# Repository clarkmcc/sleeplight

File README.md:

# SleepLight

SleepLight is a BLE-connected bedside light built around an ESP32-C3, with an iOS companion app for color and brightness control.

## Repository layout

- `firmware/` - Rust firmware for the ESP32-C3 (BLE peripheral + LED ring control).
- `ios/` - SwiftUI iOS app that scans, connects, and sends color/brightness updates over BLE.
- `hardware/` - KiCad project, manufacturing outputs, and mechanical assets (`.kicad_*`, Gerbers, STEP/STL).
- `silkscreen.ai` - Illustrator source for silkscreen/artwork.

## Quick start

### 1) Firmware (ESP32-C3)

Prereqs:
- Rust toolchain (stable) with `riscv32imc-unknown-none-elf`
- `probe-rs` installed
- ESP32-C3 board connected via debug probe

From `firmware/`:

```bash
cargo run
```

This uses the configured runner (`probe-rs run --chip esp32c3 ...`) to build and flash.

### 2) iOS app

Prereqs:
- Xcode (current version)
- iOS device or simulator with Bluetooth support (device recommended)

Open and run:
- `ios/SleepLight.xcodeproj`
- Select the `SleepLight` target and run.

The app scans for a BLE peripheral named `SleepLight` and controls RGB + brightness.

## Current BLE contract

- Peripheral name: `SleepLight`
- Light service UUID: `f3e0c001-8b6f-4d2e-a2d0-6b9c3f2a0000`
- State characteristic UUID: `f3e0c002-8b6f-4d2e-a2d0-6b9c3f2a0000`
- Payload format: 4 bytes `[R, G, B, brightness]`

## Licensing

See [licenses](./LICENSES/README.md) for scope mapping.

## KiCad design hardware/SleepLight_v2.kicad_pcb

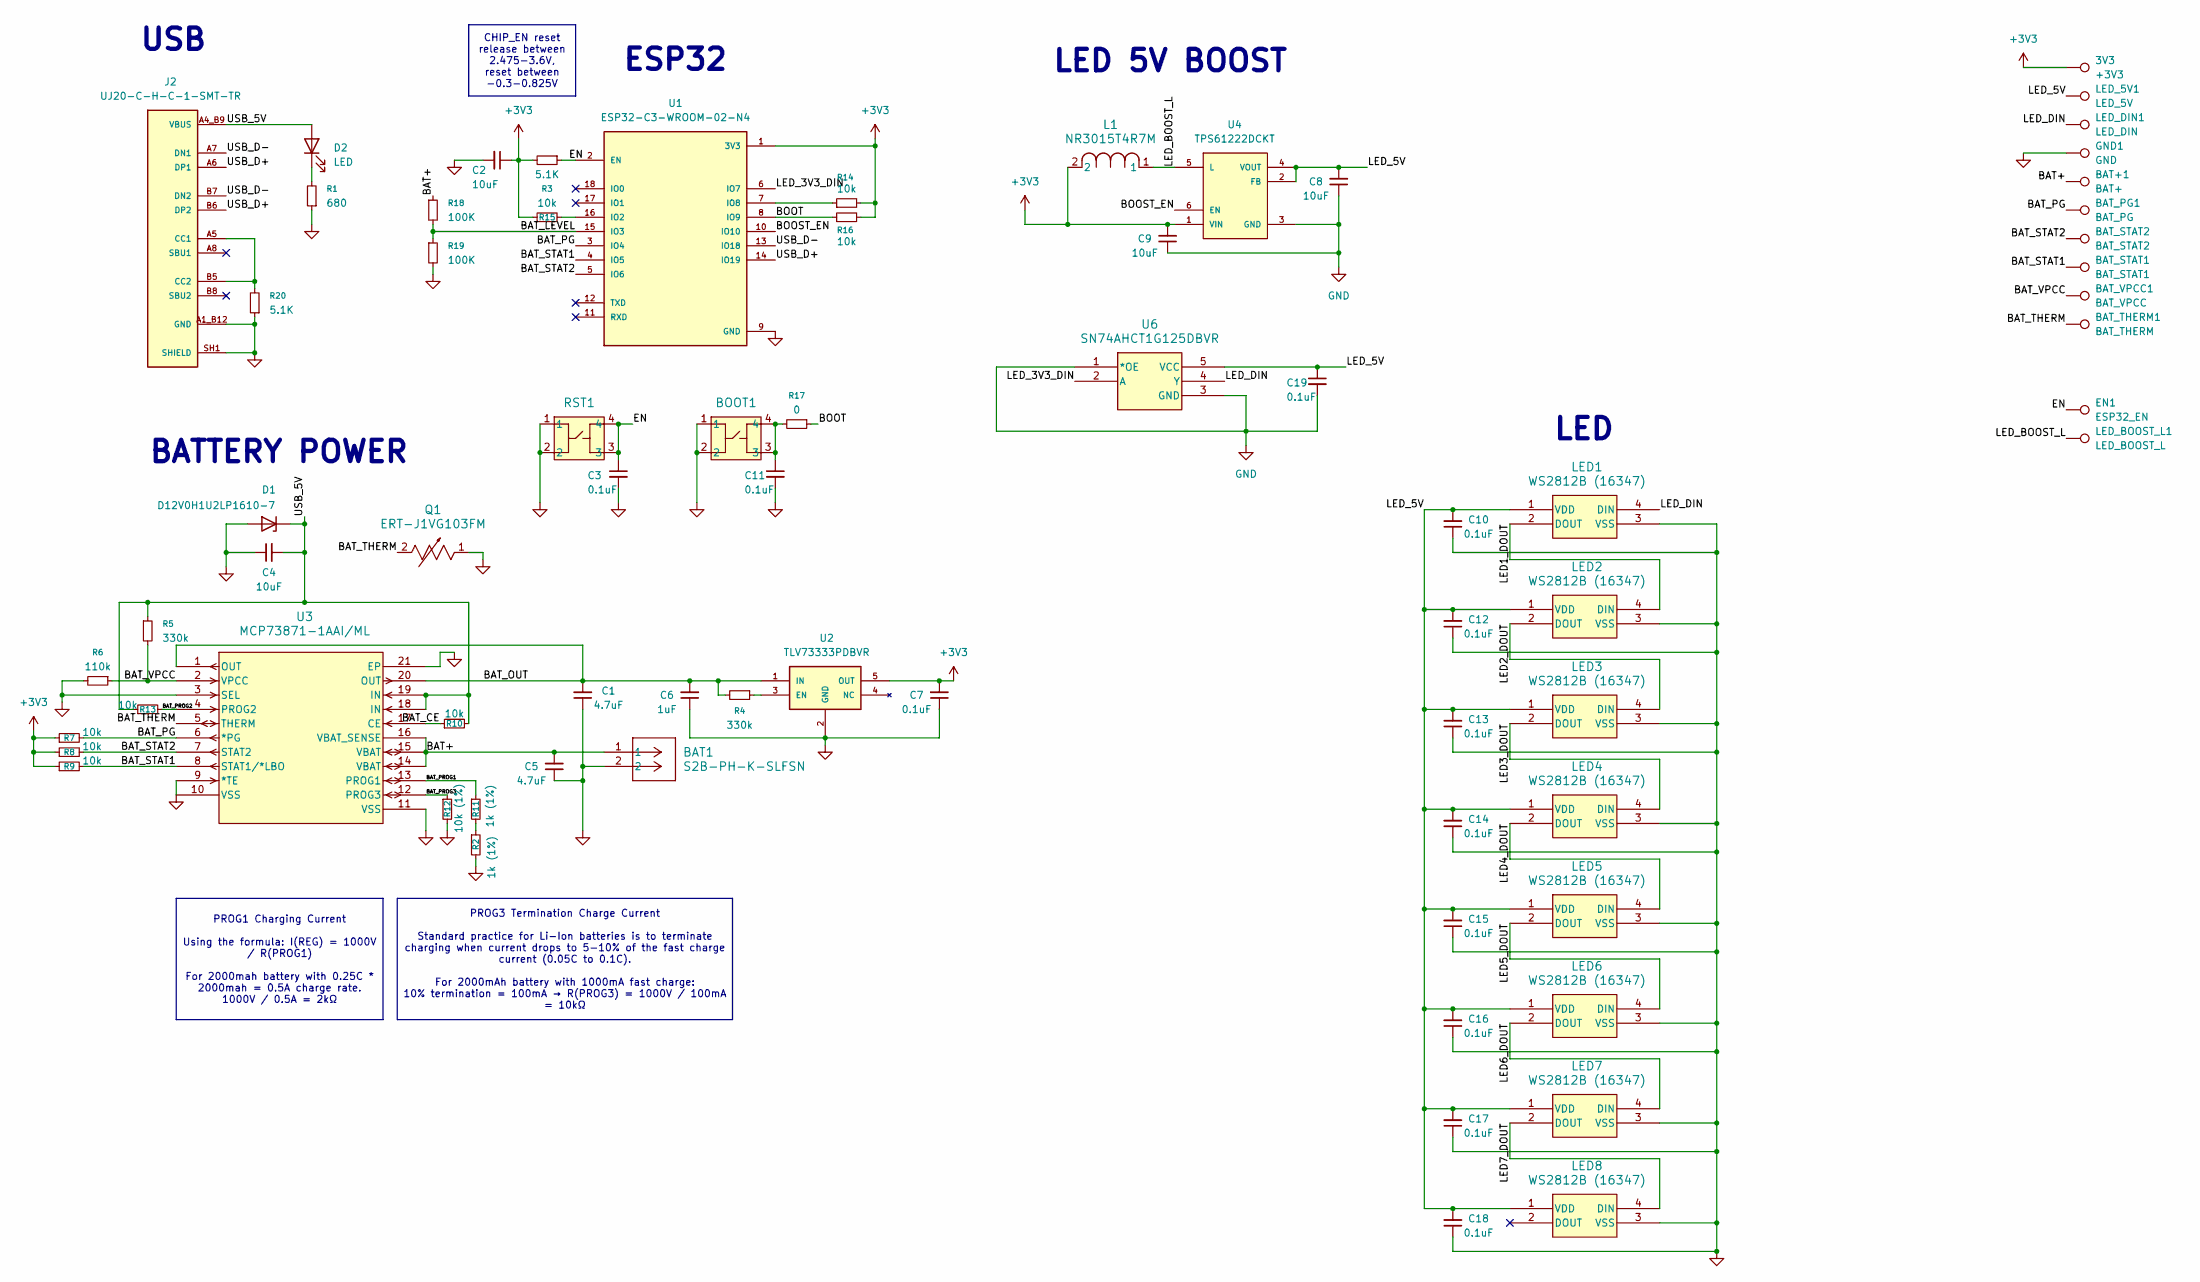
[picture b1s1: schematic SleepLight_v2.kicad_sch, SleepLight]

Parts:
3V3: +3V3; TestPoint_Pad_1.5x1.5mm
BAT1: S2B-PH-K-SLFSN; CONN_S2B-PH-K-S_JST
BAT+1: BAT+; TestPoint_Pad_1.5x1.5mm
BAT_PG1: BAT_PG; TestPoint_Pad_1.5x1.5mm
BAT_STAT1: BAT_STAT1; TestPoint_Pad_1.5x1.5mm
BAT_STAT2: BAT_STAT2; TestPoint_Pad_1.5x1.5mm
BAT_THERM1: BAT_THERM; TestPoint_Pad_1.5x1.5mm
BAT_VPCC1: BAT_VPCC; TestPoint_Pad_1.5x1.5mm
BOOT1: PTS526 SM15 SMTR2 LFS; SON4_PTS526 SM15 SMTR2 LFS_CNK
C1, C5: 4.7uF; C_0603_1608Metric
C2, C4, C8, C9: 10uF; C_0603_1608Metric
C3, C7, C10, C11, C12, C13, C14, C15, C16, C17, C18, C19: 0.1uF; C_0603_1608Metric
C6: 1uF; C_0603_1608Metric
D1: D12V0H1U2LP1610-7; D_0603_1608Metric; DigiKey_Part_Number D12V0H1U2LP1610-7DICT-ND
D2: LED; LED_0603_1608Metric; DigiKey_Part_Number 160-1478-1-ND
EN1: ESP32_EN; TestPoint_Pad_1.5x1.5mm
GND1: GND; TestPoint_Pad_1.5x1.5mm
J2: UJ20-C-H-C-1-SMT-TR; CUI_UJ20-C-H-C-1-SMT-TR; PARTREV 1.0; DigiKey_Part_Number 2223-UJ20-C-H-C-1-SMT-TRCT-ND
L1: NR3015T4R7M; IND_TAIYO_NR3015_TAY; DigiKey_Part_Number 587-1649-1-ND
LED1, LED2, LED3, LED4, LED5, LED6, LED7, LED8: WS2812B (16347); COM-16347_SPK
LED_5V1: LED_5V; TestPoint_Pad_1.5x1.5mm
LED_BOOST_L1: LED_BOOST_L; TestPoint_Pad_1.5x1.5mm
LED_DIN1: LED_DIN; TestPoint_Pad_1.5x1.5mm
Q1: ERT-J1VG103FM; TRES_ERTJ1_PAN
R1: 680; R_0603_1608Metric
R2, R11: 1k (1%); R_0603_1608Metric; DigiKey_Part_Number RMCF0603FT1K00CT-ND
R3, R20: 5.1K; R_0603_1608Metric
R4, R5: 330k; R_0603_1608Metric
R6: 110k; R_0603_1608Metric
R7, R8, R9, R10, R13, R14, R15, R16: 10k; R_0603_1608Metric
R12: 10k (1%); R_0603_1608Metric; DigiKey_Part_Number 311-10.0KHRCT-ND
R17: 0; R_0603_1608Metric
R18, R19: 100K; R_0603_1608Metric
RST1: PTS526 SM15 SMTR2 LFS; SON4_PTS526 SM15 SMTR2 LFS_CNK; DigiKey_Part_Number CKN12220-1-ND
U1: ESP32-C3-WROOM-02-N4; MODULE_ESP32-C3-WROOM-02-H4; DigiKey_Part_Number 1965-ESP32-C3-WROOM-02-N4CT-ND
U2: TLV73333PDBVR; SOT95P280X145-5N; PARTREV C
U3: MCP73871-1AAI/ML; QFN20_4x4MC_MCH; DigiKey_Part_Number MCP73871-1AAI/ML-ND
U4: TPS61222DCKT; SOT65P210X110-6N
U6: SN74AHCT1G125DBVR; DBV5

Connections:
+3V3: 3V3.1, C2.1, C7.2, C9.2, L1.2, R3.2, R7.1, R8.1, R9.1, R14.2, R15.1, R16.2, U1.1 (3V3), U2.5 (OUT), U4.1 (VIN)
/BAT+: BAT1.1, BAT+1.1, C5.2, R18.1, U3.14 (VBAT), U3.15 (VBAT), U3.16 (VBAT_SENSE)
/BAT_CE: R10.1, U3.17 (CE)
/BAT_LEVEL: R18.2, R19.1, U1.15 (IO3)
/BAT_OUT: C1.2, C6.2, R4.2, U2.1 (IN), U3.1 (OUT), U3.20 (OUT)
/BAT_PG: BAT_PG1.1, R7.2, U1.3 (IO4), U3.6 (*PG)
/BAT_PROG1: R11.1, U3.13 (PROG1)
/BAT_PROG2: R13.2, U3.4 (PROG2)
/BAT_PROG3: R12.1, U3.12 (PROG3)
/BAT_STAT1: BAT_STAT1.1, R9.2, U1.4 (IO5), U3.8 (STAT1/*LBO)
/BAT_STAT2: BAT_STAT2.1, R8.2, U1.5 (IO6), U3.7 (STAT2)
/BAT_THERM: BAT_THERM1.1, Q1.2, U3.5 (THERM)
/BAT_VPCC: BAT_VPCC1.1, R5.2, R6.1, U3.2 (VPCC)
/BOOST_EN: U1.10 (IO10), U4.6 (EN)
/BOOT: R16.1, R17.1, U1.8 (IO9)
/EN: C3.1, EN1.1, R3.1, RST1.3, RST1.4, U1.2 (EN)
/LED1_DOUT: LED1.2 (DOUT), LED2.4 (DIN)
/LED2_DOUT: LED2.2 (DOUT), LED3.4 (DIN)
/LED3_DOUT: LED3.2 (DOUT), LED4.4 (DIN)
/LED4_DOUT: LED4.2 (DOUT), LED5.4 (DIN)
/LED5_DOUT: LED5.2 (DOUT), LED6.4 (DIN)
/LED6_DOUT: LED6.2 (DOUT), LED7.4 (DIN)
/LED7_DOUT: LED7.2 (DOUT), LED8.4 (DIN)
/LED_3V3_DIN: U1.6 (IO7), U6.2 (A)
/LED_5V: C8.2, C10.2, C12.2, C13.2, C14.2, C15.2, C16.2, C17.2, C18.2, C19.1, LED1.1 (VDD), LED2.1 (VDD), LED3.1 (VDD), LED4.1 (VDD), LED5.1 (VDD), LED6.1 (VDD), LED7.1 (VDD), LED8.1 (VDD), LED_5V1.1, U4.2 (FB), U4.4 (VOUT), U6.5 (VCC)
/LED_BOOST_L: L1.1, LED_BOOST_L1.1, U4.5 (L)
/LED_DIN: LED1.4 (DIN), LED_DIN1.1, U6.4 (Y)
/USB_5V: C4.2, D1.1 (K), D2.2 (A), J2.A4_B9 (VBUS), J2.B4_A9 (VBUS), R5.1, R10.2, R13.1, U3.18 (IN), U3.19 (IN)
/USB_D+: J2.A6 (DP1), J2.B6 (DP2), U1.14 (IO19)
/USB_D-: J2.A7 (DN1), J2.B7 (DN2), U1.13 (IO18)
GND: BAT1.2, BOOT1.1, BOOT1.2, C1.1, C2.2, C3.2, C4.1, C5.1, C6.1, C7.1, C8.1, C9.1, C10.1, C11.2, C12.1, C13.1, C14.1, C15.1, C16.1, C17.1, C18.1, C19.2, D1.2 (A), GND1.1, J2.A1_B12 (GND), J2.B1_A12 (GND), J2.SH1 (SHIELD), J2.SH2 (SHIELD), J2.SH3 (SHIELD), J2.SH4 (SHIELD), J2.SH5 (SHIELD), J2.SH6 (SHIELD), LED1.3 (VSS), LED2.3 (VSS), LED3.3 (VSS), LED4.3 (VSS), LED5.3 (VSS), LED6.3 (VSS), LED7.3 (VSS), LED8.3 (VSS), Q1.1, R1.1, R2.2, R6.2, R12.2, R19.2, R20.1, RST1.1, RST1.2, U1.9 (GND), U1.19 (GND), U1.20 (GND), U1.21 (GND), U1.22 (GND), U1.23 (GND), U1.24 (GND), U1.25 (GND), U1.26 (GND), U1.27 (GND), U1.28 (GND), U1.29 (GND), U1.30 (GND), U1.31 (GND), U1.32 (GND), U1.33 (GND), U1.34 (GND), U1.35 (GND), U1.36 (GND), U1.37 (GND), U1.38 (GND), U1.39 (GND), U2.2 (GND), U3.3 (SEL), U3.9 (*TE), U3.10 (VSS), U3.11 (VSS), U3.21 (EP), U4.3 (GND), U6.1 (*OE), U6.3 (GND)
unnamed: BOOT1.3, BOOT1.4, C11.1, R17.2
unnamed: D2.1 (K), R1.2
unnamed: J2.A5 (CC1), J2.B5 (CC2), R20.2
unnamed: R2.1, R11.2
unnamed: R15.2, U1.16 (IO2)
unnamed: R14.1, U1.7 (IO8)
unnamed: R4.1, U2.3 (EN)

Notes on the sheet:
ESP32
LED
USB
LED 5V BOOST
BATTERY POWER
PROG3 Termination Charge Current Standard practice for Li-Ion batteries is to terminate charging when current drops to 5-10% of the fast charge current (0.05C to 0.1C). For 2000mAh battery with 1000mA fast charge: 10% termination = 100mA → R(PROG3) = 1000V / 100mA = 10kΩ
PROG1 Charging Current Using the formula: I(REG) = 1000V / R(PROG1) For 2000mah battery with 0.25C * 2000mah = 0.5A charge rate. 1000V / 0.5A = 2kΩ
CHIP_EN reset release between 2.475-3.6V, reset between -0.3-0.825V

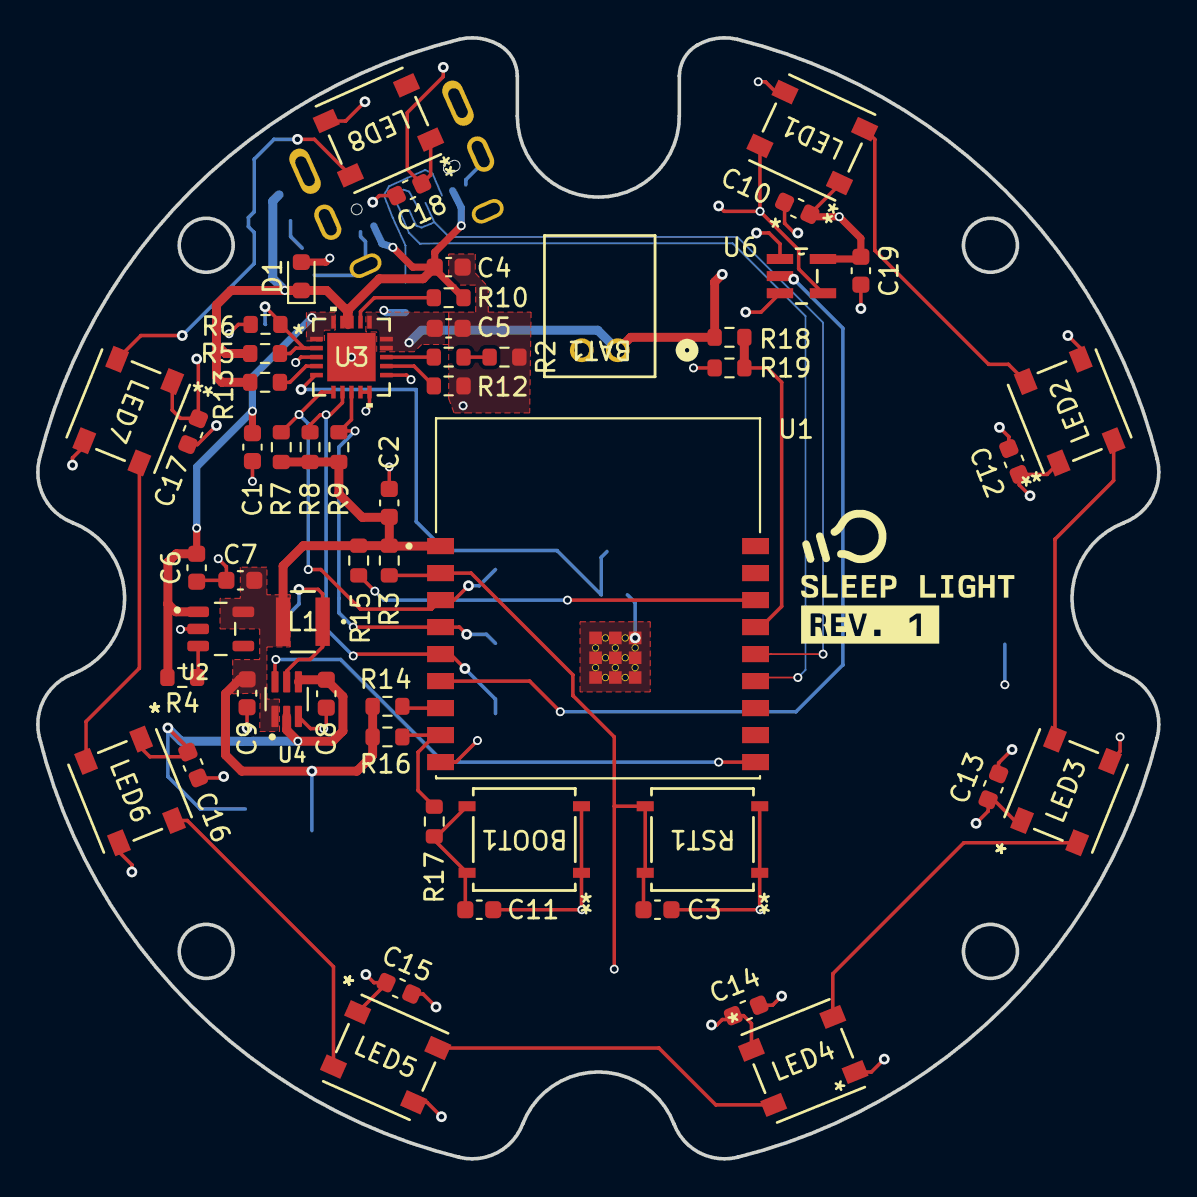
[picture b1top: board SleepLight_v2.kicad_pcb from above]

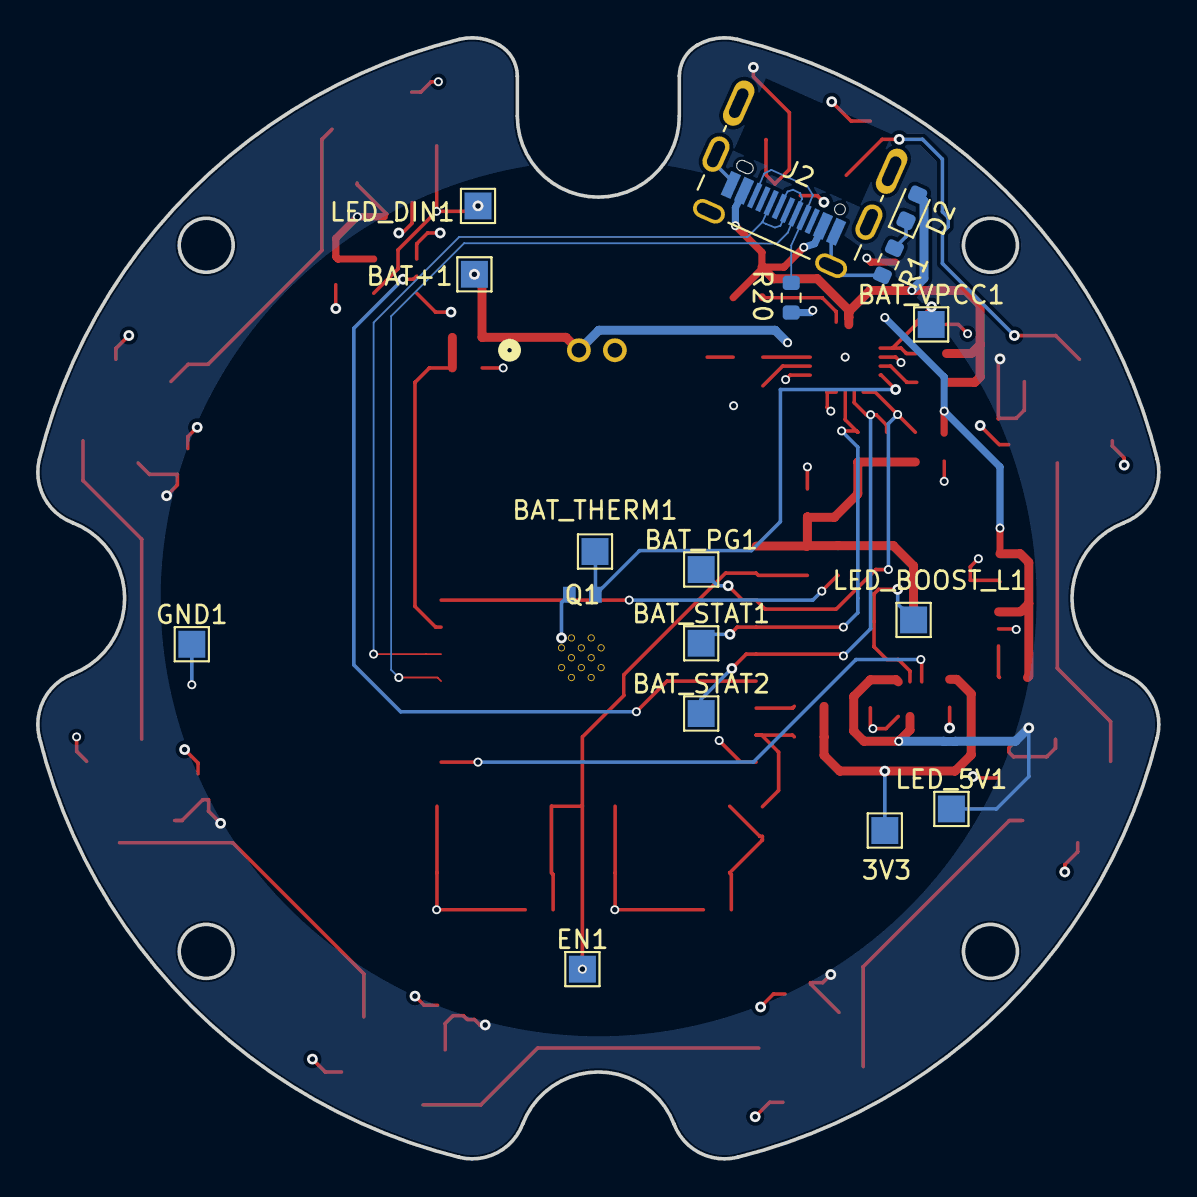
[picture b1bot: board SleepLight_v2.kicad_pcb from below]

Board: 4 copper layers, 62.3 x 62.3 mm, 72 parts (17 on the bottom side), 38 nets.

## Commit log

2026-03-03 Various cleanup items
2026-06-16 fix: ldo en pull-up resistor
2026-06-16 fix: led bypass cap positioning
